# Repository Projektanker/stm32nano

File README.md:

# STM32nano

This is a small breakout board to use the STM32F070F6Px or other pin compatible STM32F0 mikrocontrollers.

## Rendered PCB

![Rendered PCB][render]

## Pinout

![Pinout][pinout]

[render]: ./images/render.png 'Rendered PCB'
[pinout]: ./pinout/pinout.png 'Pinout'

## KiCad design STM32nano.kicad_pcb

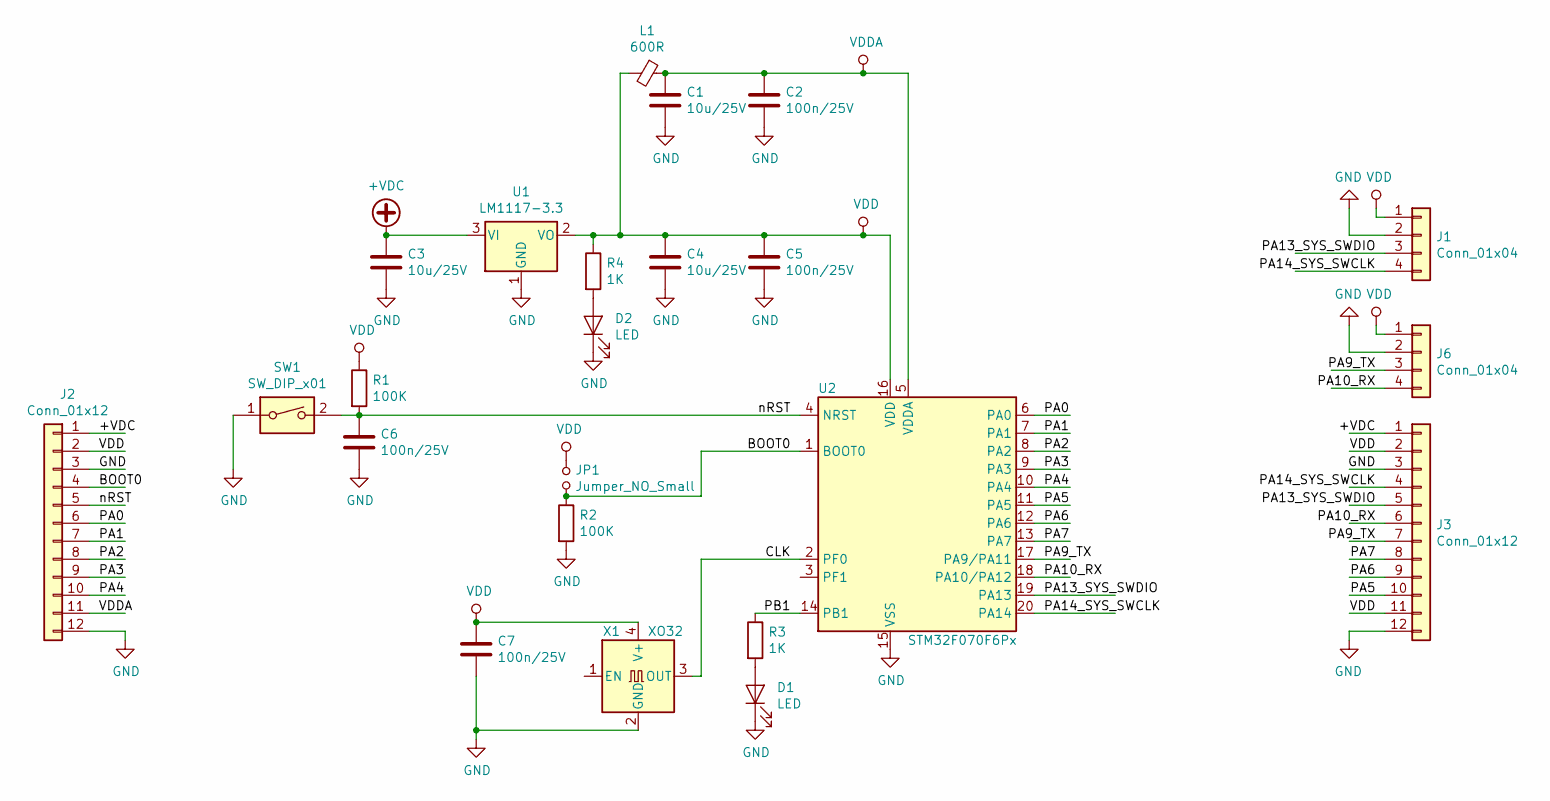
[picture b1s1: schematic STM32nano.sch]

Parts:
C1, C3, C4: 10u/25V; C_0805_2012Metric
C2, C5, C6, C7: 100n/25V; C_0603_1608Metric
D1, D2: LED; LED_0603_1608Metric
J1, J6: Conn_01x04; PinHeader_1x04_P2.54mm_Vertical
J2, J3: Conn_01x12; PinHeader_1x12_P2.54mm_Vertical
JP1: Jumper_NO_Small; PinHeader_1x02_P2.54mm_Vertical
L1: 600R; L_0603_1608Metric
R1, R2: 100K; R_0603_1608Metric
R3, R4: 1K; R_0603_1608Metric
SW1: SW_DIP_x01; SW_SPST_B3U-1000P
U1: LM1117-3.3; SOT-223-3_TabPin2
U2: STM32F070F6Px; TSSOP-20_4.4x6.5mm_P0.65mm
X1: XO32; Oscillator_SMD_EuroQuartz_XO32-4Pin_3.2x2.5mm

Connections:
+VDC: C3.1, J2.1, J3.1, U1.3 (VI)
/BOOT0: J2.4, JP1.2, R2.1, U2.1 (BOOT0)
/CLK: U2.2 (PF0), X1.3 (OUT)
/PA0: J2.6, U2.6 (PA0)
/PA1: J2.7, U2.7 (PA1)
/PA2: J2.8, U2.8 (PA2)
/PA3: J2.9, U2.9 (PA3)
/PA4: J2.10, U2.10 (PA4)
/PA5: J3.10, U2.11 (PA5)
/PA6: J3.9, U2.12 (PA6)
/PA7: J3.8, U2.13 (PA7)
/PA9_TX: J3.7, J6.3, U2.17 (PA9/PA11)
/PA10_RX: J3.6, J6.4, U2.18 (PA10/PA12)
/PA13_SYS_SWDIO: J1.3, J3.5, U2.19 (PA13)
/PA14_SYS_SWCLK: J1.4, J3.4, U2.20 (PA14)
/PB1: R3.1, U2.14 (PB1)
/nRST: C6.1, J2.5, R1.2, SW1.2, U2.4 (NRST)
GND: C1.2, C2.2, C3.2, C4.2, C5.2, C6.2, C7.2, D1.1 (K), D2.1 (K), J1.2, J2.3, J2.12, J3.3, J3.12, J6.2, R2.2, SW1.1, U1.1 (GND), U2.15 (VSS), X1.2 (GND)
unnamed: D1.2 (A), R3.2
unnamed: D2.2 (A), R4.2
VDD: C4.1, C5.1, C7.1, J1.1, J2.2, J3.2, J3.11, J6.1, JP1.1, L1.2, R1.1, R4.1, U1.2 (VO), U2.16 (VDD), X1.4 (V+)
VDDA: C1.1, C2.1, J2.11, L1.1, U2.5 (VDDA)

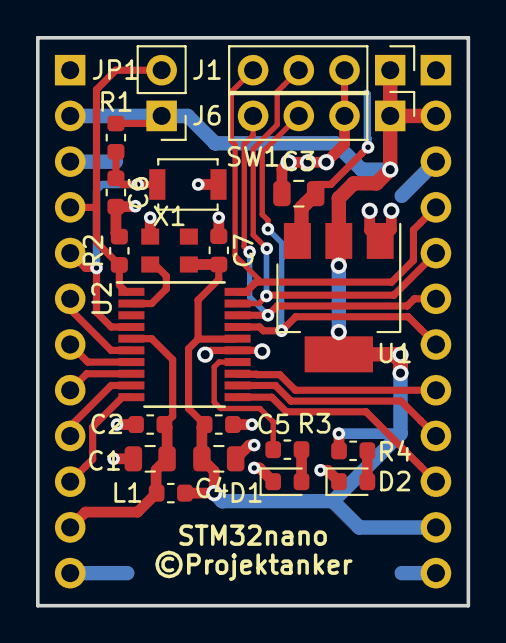
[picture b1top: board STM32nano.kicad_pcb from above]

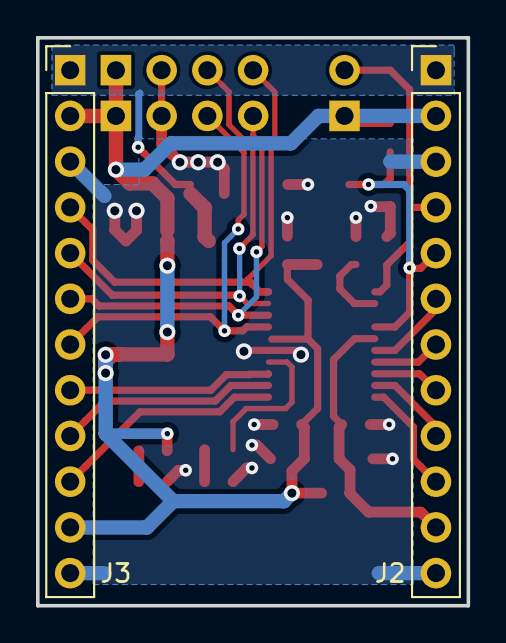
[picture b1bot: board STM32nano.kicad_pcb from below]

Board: 2 copper layers, 23.9 x 31.5 mm, 23 parts (2 on the bottom side), 22 nets.

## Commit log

2019-01-29 pcb updated and plotted
2019-02-28 Modified gerber files to jlcpcb.com requirements removed BOM rerendered PCB
2019-02-28 added top.png; moved images to images folder
2019-02-28 pinout added
2019-02-28 croped render.png
2019-02-28 added README

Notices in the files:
STM32nano.kicad_pcb:
©Projektanker
